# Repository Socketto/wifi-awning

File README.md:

# Project Overview: Wind Alarm Awning Control Replacement System

This project was developed to replace a faulty awning control board that is triggered in case of high wind conditions. The system uses an anemometer to detect wind speed, and through a control board equipped with an onboard trimmer, it allows the user to set a wind speed threshold. Once this threshold is exceeded, the awning is automatically retracted to prevent wind damage.

## Original Control Board: Firmware Bug

The original board, while functional in normal conditions, presents a critical firmware issue. Below is a step-by-step breakdown of the standard operation and the bug scenario:

### Normal Operation:
1. The awning is lowered via manual or remote control.
2. The board executes the command and lowers the awning.
3. If wind speed exceeds the set threshold, the board retracts the awning and leaves it retracted.

### Bug Scenario:
1. The awning is lowered using the control commands.
2. The board properly lowers the awning.
3. Upon high wind detection, the board retracts the awning as expected.
4. While outside the building, the user manually lowers the awning using the crank handle.
5. The board does not detect that the awning was manually lowered.
6. If wind conditions worsen again, the board fails to retract the awning, leaving it exposed to damage.

## New Control Board: Fully Programmable and Wi-Fi Enabled

The replacement board is fully programmable, supporting both Arduino and ESP-IDF environments. This flexibility allows for quick and permanent fixes to firmware bugs like the one described above. Additionally, the board natively supports Wi-Fi connectivity for remote monitoring and updates.

## Advanced Features:

- **Current Sensor Integration:**  
  A current sensor is integrated directly on the board and connected to an ADC1 pin. This feature enables the system to control the awning opening to a specific percentage. Once programmed with a calibration sequence, the system can learn and control precise positions.

- **Debug and Display Capabilities:**
  - **Serial Interface:** For real-time debugging and logging.
  - **RGB LED:** Programmable for visual status indicators.
  - **LCD Display Support:** Allows the connection of an LCD screen to show system status and operational feedback.

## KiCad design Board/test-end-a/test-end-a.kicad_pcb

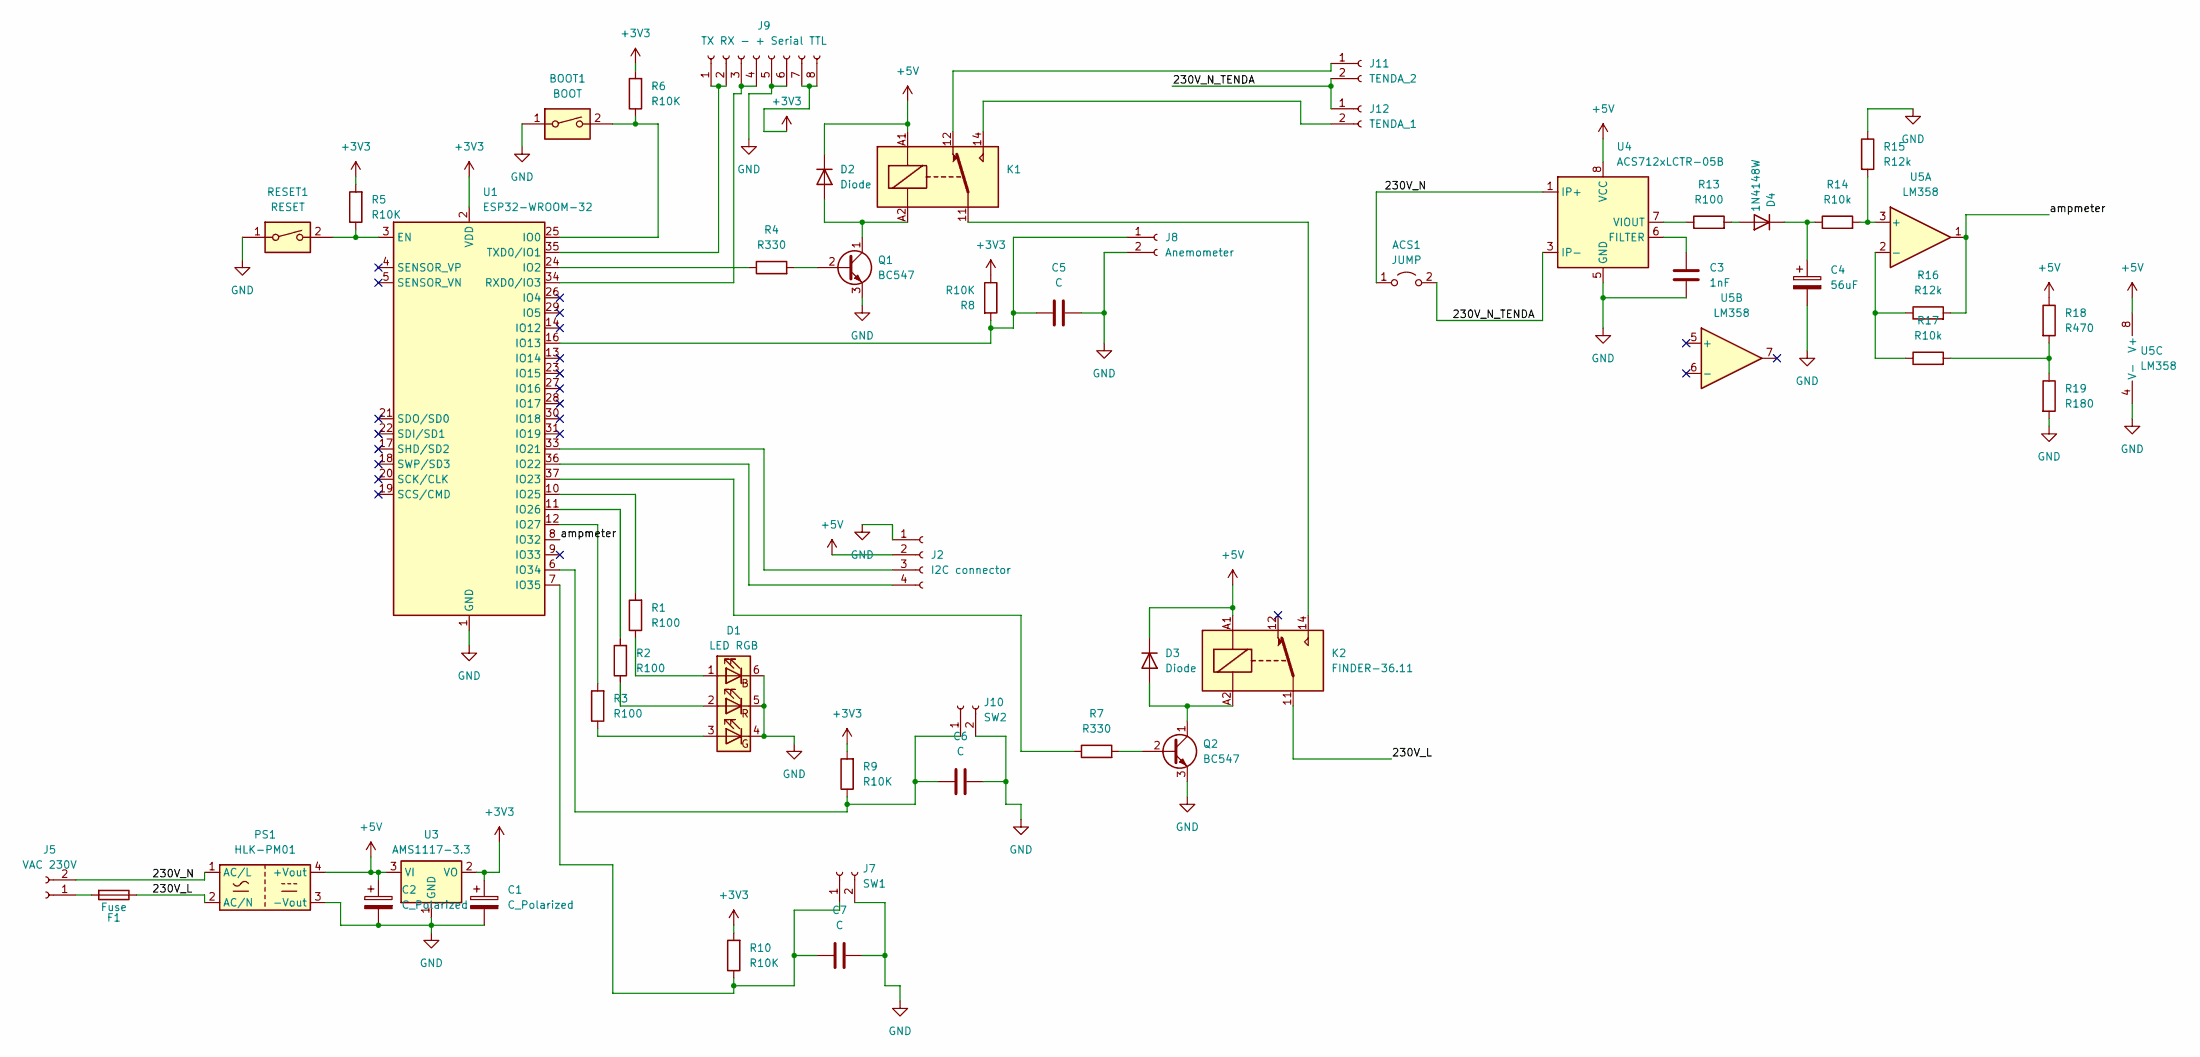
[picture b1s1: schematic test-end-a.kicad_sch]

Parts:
ACS1: JUMP; SolderJumper-2_P1.3mm_Open_RoundedPad1.0x1.5mm
BOOT1: BOOT; SW_PUSH_6mm_H4.3mm
C1, C2: C_Polarized; CP_Radial_D10.0mm_P5.00mm
C3: 1nF; L_1206_3216Metric_Pad1.22x1.90mm_HandSolder
C4: 56uF; CP_Radial_D10.0mm_P5.00mm
C5, C6, C7: C; C_Disc_D8.0mm_W2.5mm_P5.00mm
D1: LED RGB; LED_RGB_5050-6
D2, D3: Diode; D_DO-35_SOD27_P10.16mm_Horizontal
D4: 1N4148W; D_SOD-123
F1: Fuse; Fuseholder_Cylinder-5x20mm_Schurter_0031_8201_Horizontal_Op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
J2: I2C connector; PinHeader_1x04_P2.54mm_Vertical
J5: VAC 230V; TerminalBlock_Altech_AK300-2_P5.00mm
J7: SW1; TerminalBlock_Altech_AK300-2_P5.00mm
J8: Anemometer; TerminalBlock_Altech_AK300-2_P5.00mm
J9: TX RX - + Serial TTL; PinSocket_2x04_P2.54mm_Vertical
J10: SW2; TerminalBlock_Altech_AK300-2_P5.00mm
J11: TENDA_2; TerminalBlock_Altech_AK300-2_P5.00mm
J12: TENDA_1; TerminalBlock_Altech_AK300-2_P5.00mm
K1, K2: FINDER-36.11; Relay_SPDT_Finder_36.11
PS1: HLK-PM01; Converter_ACDC_Hi-Link_HLK-PMxx
Q1, Q2: BC547; TO-92_Inline
R1, R2, R3, R13: R100; R_1206_3216Metric
R4, R7: R330; R_1206_3216Metric
R5, R6, R8, R9, R10: R10K; R_1206_3216Metric
R14, R17: R10k; R_1206_3216Metric
R15, R16: R12k; R_1206_3216Metric
R18: R470; R_1206_3216Metric
R19: R180; R_1206_3216Metric
RESET1: RESET; SW_PUSH_6mm_H4.3mm
U1: ESP32-WROOM-32
U3: AMS1117-3.3; SOT-223-3_TabPin2
U4: ACS712xLCTR-05B; SOIC-8_3.9x4.9mm_P1.27mm
U5: LM358; SOIC-8-1EP_3.9x4.9mm_P1.27mm_EP2.29x3mm

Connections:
+3V3: C1.1, J9.7, J9.8, R5.2, R6.2, R8.1, R9.2, R10.2, U1.2 (VDD), U3.2 (VO)
+5V: C2.1, D2.1 (K), D3.1 (K), J2.2, K1.A1, K2.A1, PS1.4 (+Vout), R18.1, U3.3 (VI), U4.8 (VCC), U5.8 (V+)
/230V_L: F1.1, K2.11, PS1.2 (AC/N)
/230V_N: ACS1.1 (A), J5.2, PS1.1 (AC/L), U4.1 (IP+), U4.2 (IP+)
/230V_N_TENDA: ACS1.2 (B), J11.2, J12.1, U4.3 (IP-), U4.4 (IP-)
/ampmeter: R16.2, U1.8 (IO32), U5.1
GND: BOOT1.1, C1.2, C2.2, C3.2, C4.2, C5.2, C6.2, C7.2, D1.4 (GK), D1.5 (RK), D1.6 (BK), J2.1, J7.2, J8.2, J9.5, J9.6, J10.2, PS1.3 (-Vout), Q1.3 (E), Q2.3 (E), R15.1, R19.2, RESET1.1, U1.1 (GND), U1.15 (GND), U1.38 (GND), U1.39 (GND), U3.1 (GND), U4.5 (GND), U5.4 (V-)
unnamed: D1.1 (BA), R1.1
unnamed: D1.3 (GA), R3.1
unnamed: D1.2 (RA), R2.1
unnamed: D2.2 (A), K1.A2, Q1.1 (C)
unnamed: D3.2 (A), K2.A2, Q2.1 (C)
unnamed: D4.2 (A), R13.2
unnamed: C4.1, D4.1 (K), R14.1
unnamed: J2.3, U1.33 (IO21)
unnamed: J2.4, U1.36 (IO22)
unnamed: F1.2, J5.1
unnamed: C7.1, J7.1, R10.1, U1.7 (IO35)
unnamed: C5.1, J8.1, R8.2, U1.16 (IO13)
unnamed: J9.1, J9.2, U1.35 (TXD0/IO1)
unnamed: J9.3, J9.4, U1.34 (RXD0/IO3)
unnamed: C6.1, J10.1, R9.1, U1.6 (IO34)
unnamed: J11.1, K1.12
unnamed: J12.2, K1.14
unnamed: K1.11, K2.14
unnamed: Q1.2 (B), R4.2
unnamed: Q2.2 (B), R7.2
unnamed: R17.2, R18.2, R19.1
unnamed: R5.1, RESET1.2, U1.3 (EN)
unnamed: BOOT1.2, R6.1, U1.25 (IO0)
unnamed: R4.1, U1.24 (IO2)
unnamed: R7.1, U1.37 (IO23)
unnamed: R1.2, U1.10 (IO25)
unnamed: R2.2, U1.11 (IO26)
unnamed: R3.2, U1.12 (IO27)
unnamed: C3.1, U4.6 (FILTER)
unnamed: R13.1, U4.7 (VIOUT)
unnamed: R14.2, R15.2, U5.3 (+)
unnamed: R16.1, R17.1, U5.2 (-)

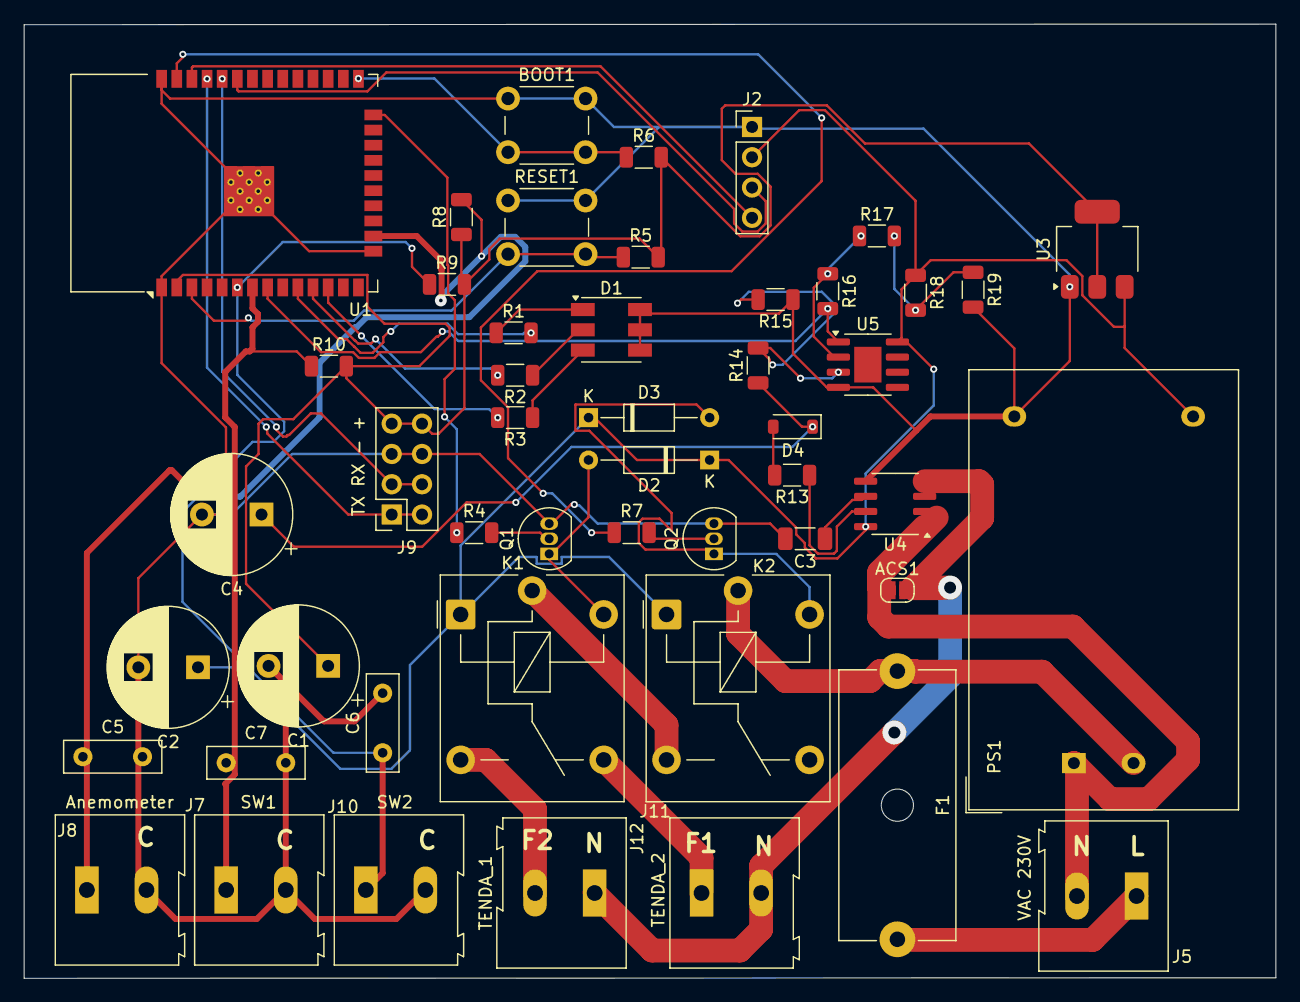
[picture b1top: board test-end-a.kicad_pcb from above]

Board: 2 copper layers, 105.0 x 80.0 mm, 49 parts (0 on the bottom side), 39 nets.

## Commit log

2025-05-31 [FIRST] First commit of awning
2025-05-31 [ADD] Add consumption scheme and components on the board
2025-05-31 [ENH] Move a wire to avoid interferences with high voltage
2025-06-15 [UPD] Update firmware with board pinout
2025-06-16 [ADD] Add management of delay between alarms
2025-06-16 [UPD] Update led color
2025-06-16 [UPD] Add management for LCD
2025-06-17 [ENH] Use 7 minutes instead of 10
2025-06-18 [FIX] Fix board dimensions
2025-06-20 [ADD] Add labels
2025-07-17 [FIX] Stable version
2025-07-18 [UPD] Update with messages and wifi status
2025-07-18 [ENH] Enhance abnormal consuption alarm
2025-07-18 [FIX] Fix first status message
2025-07-18 [ENH] Enhance alarm check
2025-07-24 [ENH] Enhanced management without current sensor
2025-08-08 [UPD] Update to git the version of firmware saved in my PC
2025-08-09 [ENH] Enhance wifi management
2025-08-12 [ENH] Enhance firmware logs
2025-08-14 [UPD] Updated status and log messages
2025-08-14 [ENH] Enhance check of Wi-Fi
2025-09-09 [ADD] Add watchdog
2025-09-09 [FIX] Fix init watchdog with new API
